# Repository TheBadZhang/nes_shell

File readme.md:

# 掌上 NES 游戏机
> 也不只是游戏机

基于 STM32H7B0VBT6 设计的 NES 掌上游戏机

包含 ESP8684 组成的 wifi 蓝牙 扩展
STM32G431CBU6 的可编程输入控制

本项目基于 weact stm32h7b0 开发板而来，主要用于学习 stm32h7b0 的使用。
移植了大量的有趣的程序，包括但不限于：

贪吃蛇、汉诺塔、俄罗斯方块

一些动画

ui效果

按键驱动

音频采集与输出

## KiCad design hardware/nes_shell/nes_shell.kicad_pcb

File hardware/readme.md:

archive       - 归档文件，一些废弃的工作
nes_shell     - 主板（包含主要计算功能）（不包含音频输入输出（可能考虑包含），不包含HDMI、VGA等显示输出）
key_board     - 按键子板（包含按键、LED、蜂鸣器等）
media_board   - 多媒体子板（包含音频输入输出、HDMI、VGA等显示输出）
pmod_extender - PMOD扩展板（包含PMOD接口）
screen_module_st7789 - st7789 屏幕模块（包含IPS LCD、WiFi、蓝牙、SD卡等）

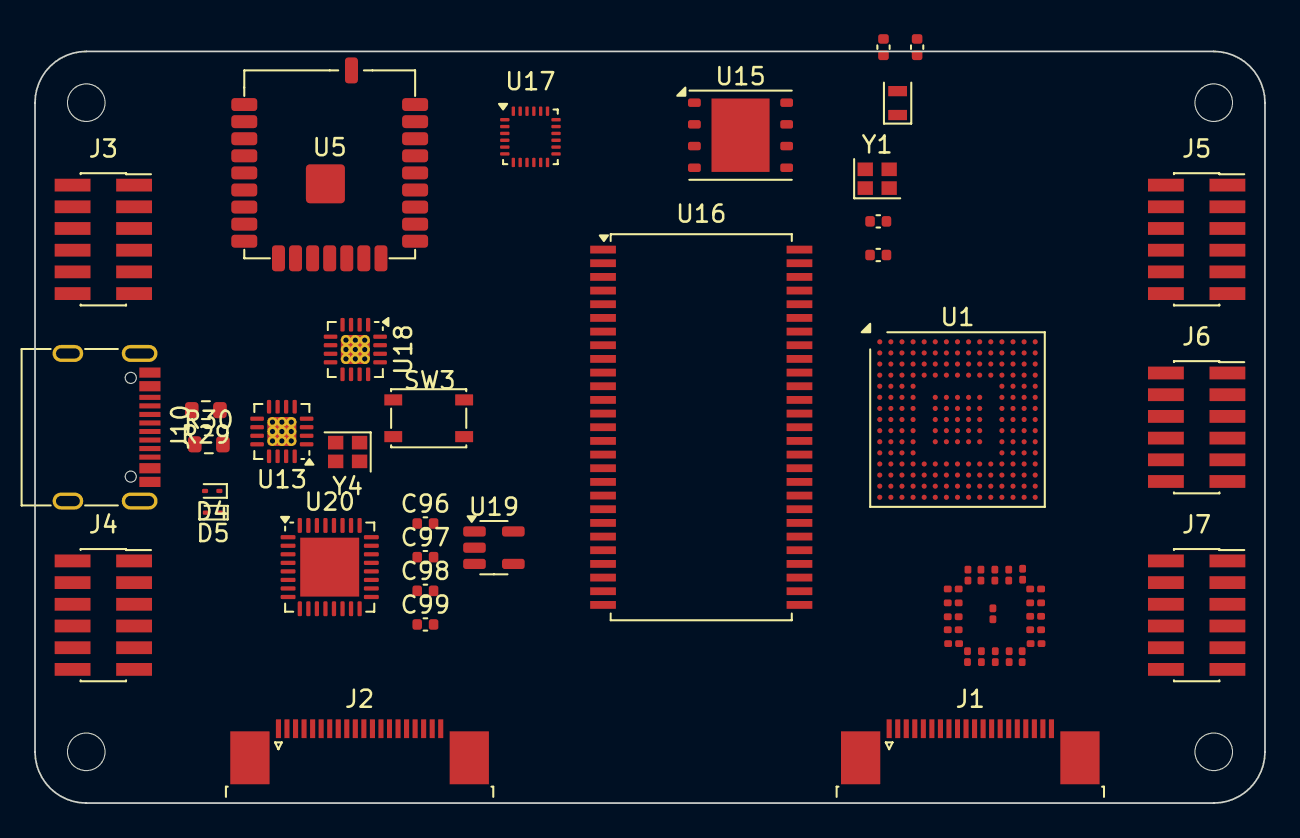
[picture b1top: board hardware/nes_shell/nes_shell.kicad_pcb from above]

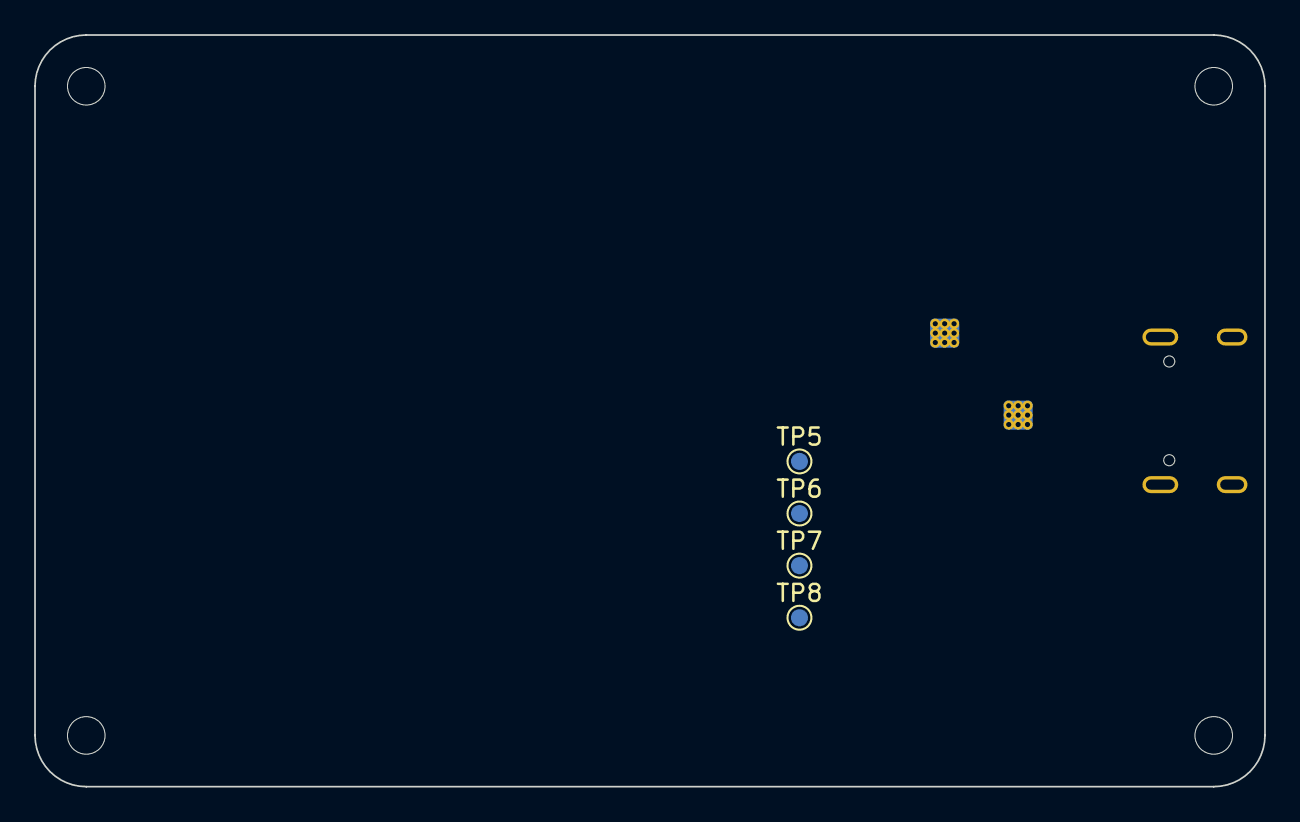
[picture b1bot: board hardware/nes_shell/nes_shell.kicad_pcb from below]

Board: 6 copper layers, 72.0 x 44.0 mm, 62 parts (4 on the bottom side), 23 nets, no tracks yet.

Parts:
C5, C18: 1.5pF; C_0402_1005Metric
C6, C7: 8pF; C_0402_1005Metric
C8, C9, C10, C11, C12, C13, C14, C15, C16, C17, C19, C20, C21, C22, C23, C24, C25, C26, C27, C28, C29: 0.1uF; C_0201_0603Metric
C96, C99: 4.7uF; C_0402_1005Metric
C97: 0.1uF; C_0402_1005Metric
C98: 22nF; C_0402_1005Metric
D4, D5: ESD9B3.3ST5G; D_SOD-923
H1, H2, H3, H4: MountingHole; MountingHole_2.2mm_M2
J1, J2: Conn_01x20_MountingPin; TE_2-1734839-0_1x20-1MP_P0.5mm_Horizontal
J3, J4, J5, J6, J7: Conn_02x06_Odd_Even; PinSocket_2x06_P1.27mm_Vertical_SMD
J10: USB_C_Receptacle_USB2.0_16P; USB_C_Receptacle_G-Switch_GT-USB-7010ASV
R29, R30: 5.1K; R_0603_1608Metric
SW3: SW_Push; KEY-SMD_4P-L4.2-W3.4-P2.15-LS4.5-TL
TP5: hub_ldo_3v3; TestPoint_Pad_D1.0mm
TP6: hub_gnd; TestPoint_Pad_D1.0mm
TP7: DMU; TestPoint_Pad_D1.0mm
TP8: DPU; TestPoint_Pad_D1.0mm
U1: STM32H7B0IBKxQ; UFBGA-201_10x10mm_Layout15x15_P0.65mm
U5: M0S
U13: CH334P; QFN-16-1EP_3x3mm_P0.5mm_EP1.7x1.7mm_ThermalVias
U15: W25Q32JVZP; WSON-8-1EP_6x5mm_P1.27mm_EP3.4x4.3mm
U16: MT48LC16M16A2TG; TSOP-II-54_22.2x10.16mm_P0.8mm
U17: MPU-9250; InvenSense_QFN-24_3x3mm_P0.4mm
U18: CH343P; QFN-16-1EP_3x3mm_P0.5mm_EP1.7x1.7mm_ThermalVias
U19: RT9193-33GB; SOT-23-5
U20: USB3300-EZK; QFN-32-1EP_5x5mm_P0.5mm_EP3.45x3.45mm
Y1: Crystal_GND24; Crystal_SMD_2016-4Pin_2.0x1.6mm
Y2: Crystal; Crystal_SMD_2012-2Pin_2.0x1.2mm
Y4: 12M; Crystal_SMD_2016-4Pin_2.0x1.6mm

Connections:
+1V8: U1.A3 (VDDLDO), U1.A13 (VDDLDO), U1.R14 (VDDLDO)
+3V3: C8.1, C9.1, C10.1, C11.1, C12.1, C13.1, C14.1, C15.1, C16.1, C17.1, C19.1, C20.1, C21.1, C22.1, C23.1, C24.1, C25.1, C26.1, C27.1, C28.1, C29.1, SW3.2, U1.D11 (VDD), U1.E4 (VDD), U1.E12 (VDD), U1.E15 (VDD50_USB), U1.F13 (VDD33_USB), U1.G4 (VDD), U1.H12 (VDD), U1.K4 (VDD), U1.L12 (VDD), U1.M5 (VDD), U1.M9 (VDD), U5.2 (VDD3V3), U15.8 (VCC), U16.1 (VDD), U16.3 (VDDQ), U16.9 (VDDQ), U16.14 (VDD), U16.27 (VDD), U16.43 (VDDQ), U16.49 (VDDQ)
/OSC32_IN: C5.1, U1.D2 (PC14), Y2.2
/OSC32_OUT: C18.1, U1.D1 (PC15), Y2.1
/OSC_IN: C6.1, U1.J1 (PH0), Y1.1
/OSC_OUT: C7.1, U1.K1 (PH1), Y1.3
/USB通信/CH343P/3V3: U18.3 (VDD5), U18.6 (V3), U18.9 (VBUS)
/USB通信/CH343P/D+: U13.8 (DP2), U18.7 (UD+)
/USB通信/CH343P/D-: U13.7 (DM2), U18.8 (UD-)
/USB通信/M0S-daplink/BOOT: SW3.1, U5.23 (GPIO2)
/USB通信/M0S-daplink/USB_DM: U5.13 (USB_DN), U13.9 (DM1)
/USB通信/M0S-daplink/USB_DP: U5.12 (USB_DP), U13.10 (DP1)
/USB通信/RT9193/+3V3: C99.2, TP5.1, U13.15 (V5), U13.16 (VDD33), U19.5 (Vout)
/USB通信/RT9193/+5V: C96.1, C97.1, U19.1 (Vin), U19.3 (EN)
/USB通信/USB_D+: D5.2 (A2), J10.A6 (D+), J10.B6 (D+), TP8.1, U13.12 (DPU)
/USB通信/USB_D-: D4.2 (A2), J10.A7 (D-), J10.B7 (D-), TP7.1, U13.11 (DMU)
GND: C5.2, C6.2, C7.2, C8.2, C9.2, C10.2, C11.2, C12.2, C13.2, C14.2, C15.2, C16.2, C17.2, C18.2, C19.2, C20.2, C21.2, C22.2, C23.2, C24.2, C25.2, C26.2, C27.2, C28.2, C29.2, C96.2, C97.2, C98.2, C99.1, D4.1 (A1), D5.1 (A1), J10.A1 (GND), J10.A12 (GND), J10.B1 (GND), J10.B12 (GND), J10.S1 (SHIELD), R29.1, R30.1, TP6.1, U1.A1 (VSS), U1.A15 (VSS), U1.C2 (VSS), U1.D6 (VSS), U1.D10 (VSS), U1.E1 (VSS), U1.F2 (VSSSMPS), U1.F6 (VSS), U1.F7 (VSS), U1.F8 (VSS), U1.F9 (VSS), U1.F10 (VSS), U1.F12 (VSS), U1.G6 (VSS), U1.G7 (VSS), U1.G8 (VSS), U1.G9 (VSS), U1.G10 (VSS), U1.H6 (VSS), U1.H7 (VSS), U1.H8 (VSS), U1.H9 (VSS), U1.H10 (VSS), U1.J6 (VSS), U1.J7 (VSS), U1.J8 (VSS), U1.J9 (VSS), U1.J10 (VSS), U1.J14 (VSS), U1.K2 (VSS), U1.K6 (VSS), U1.K7 (VSS), U1.K8 (VSS), U1.K9 (VSS), U1.K10 (VSS), U1.K12 (VSS), U1.M6 (VSS), U1.M10 (VSS), U1.N3 (VSSA), U1.R1 (VSS), U1.R15 (VSS), U5.1 (GND), U5.25 (GND), U5.27 (EPAD), U15.4 (GND), U15.9 (EP), U16.6 (VSSQ), U16.12 (VSSQ), U16.28 (VSS), U16.41 (VSS), U16.46 (VSSQ), U16.52 (VSSQ), U16.54 (VSS), U19.2 (GND), Y1.2, Y1.4, Y4.2, Y4.4
unnamed: J10.A5 (CC1), R29.2
unnamed: J10.B5 (CC2), R30.2
unnamed: U13.2 (XI), Y4.1
unnamed: U13.1 (XO), Y4.3
unnamed: C98.1, U19.4 (BP)
VBUS: J10.A4 (VBUS), J10.A9 (VBUS), J10.B4 (VBUS), J10.B9 (VBUS)

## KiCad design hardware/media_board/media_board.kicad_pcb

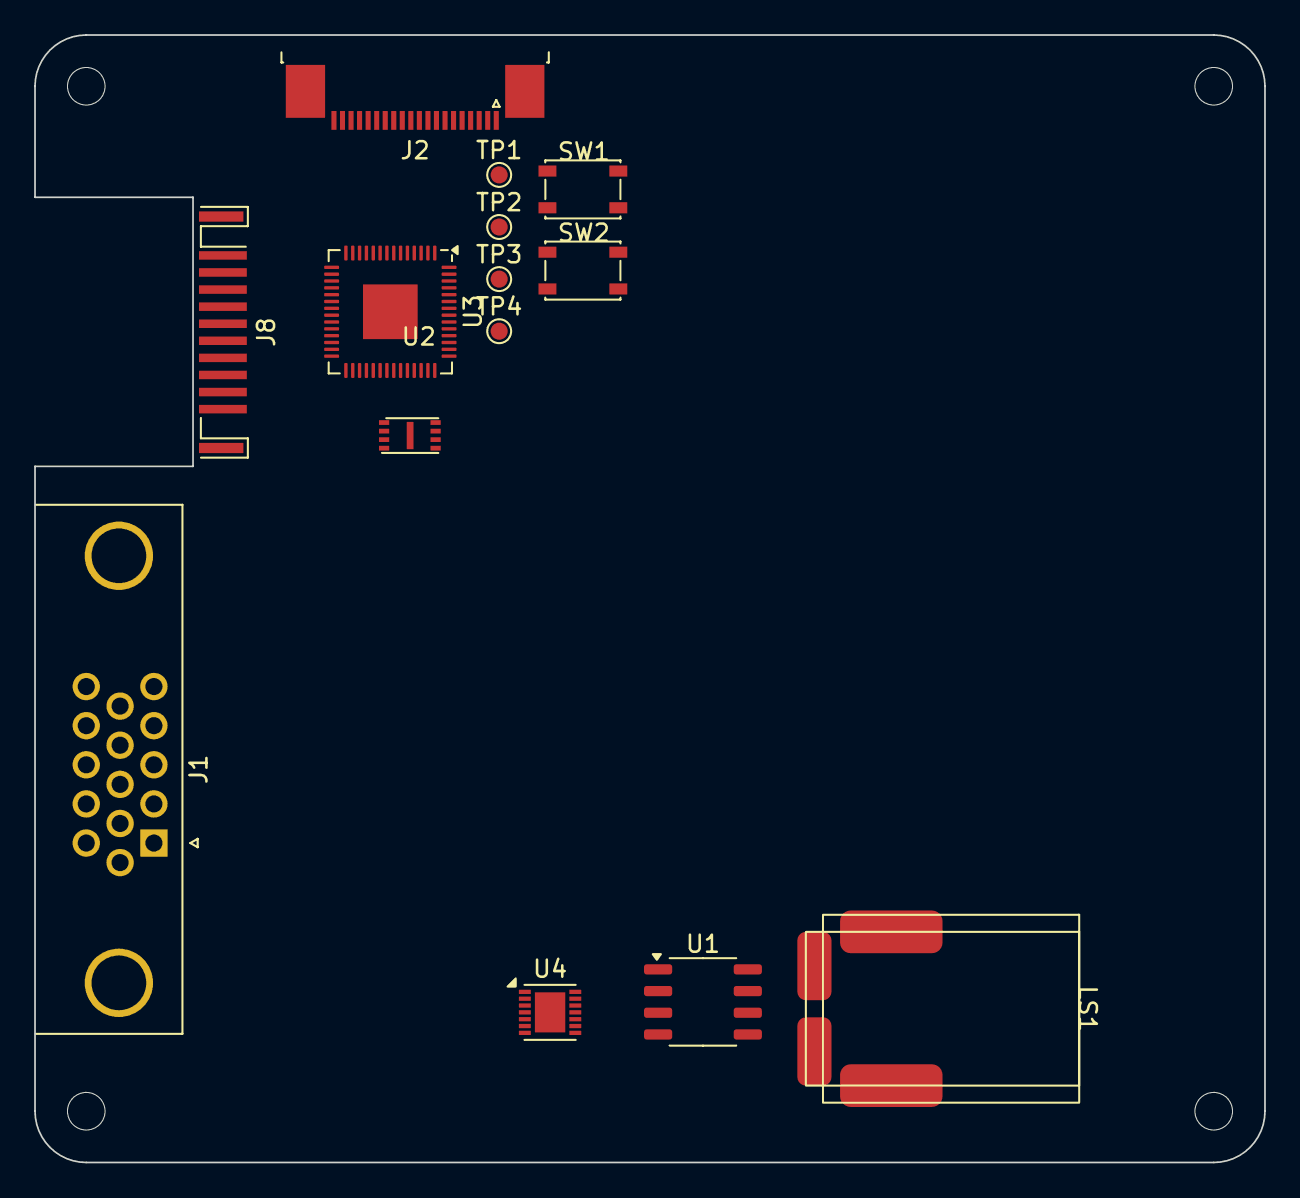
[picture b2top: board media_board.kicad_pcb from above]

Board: 2 copper layers, 72.0 x 66.0 mm, 18 parts (0 on the bottom side), 24 nets, no tracks yet.

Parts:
H1, H2, H3, H4: MountingHole; MountingHole_2.2mm_M2
J1: DE15_Plug_HighDensity_MountingHoles; DSUB-15-HD_Female_Horizontal_P2.29x1.98mm_EdgePinOffset3.03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
J2: Conn_01x20_MountingPin; TE_2-1734839-0_1x20-1MP_P0.5mm_Horizontal
J8: HDMI_A; HDMI_A_Contact_Technology_HDMI-19APL2_Horizontal
LS1: Speaker; speaker_1511_1609
SW1, SW2: SW_Push; KEY-SMD_4P-L4.2-W3.4-P2.15-LS4.5-TL
TP1, TP2, TP3, TP4: TestPoint; TestPoint_Pad_D1.0mm
U1: FM8002A; SOP-8_3.9x4.9mm_P1.27mm
U2: W25Q16; USON-8
U3: RP2040; QFN-56-1EP_7x7mm_P0.4mm_EP3.2x3.2mm
U4: MAX9814; DFN-14-1EP_3x3mm_P0.4mm_EP1.78x2.35mm

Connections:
+1V1: U3.23 (DVDD), U3.45 (VREG_VOUT), U3.50 (DVDD)
+3V3: TP1.1, U2.8 (VCC), U3.1 (IOVDD), U3.10 (IOVDD), U3.22 (IOVDD), U3.33 (IOVDD), U3.42 (IOVDD), U3.43 (ADC_AVDD), U3.44 (VREG_IN), U3.48 (USB_VDD), U3.49 (IOVDD), U4.2 (~SHDN), U4.5 (VDD)
/rp2040_hdmi/DVI_CK+: J8.10 (CK+), U3.12 (GPIO9)
/rp2040_hdmi/DVI_CK-: J8.12 (CK-), U3.11 (GPIO8)
/rp2040_hdmi/DVI_D0+: J8.7 (D0+), U3.14 (GPIO11)
/rp2040_hdmi/DVI_D0-: J8.9 (D0-), U3.13 (GPIO10)
/rp2040_hdmi/DVI_D1+: J8.4 (D1+), U3.16 (GPIO13)
/rp2040_hdmi/DVI_D1-: J8.6 (D1-), U3.15 (GPIO12)
/rp2040_hdmi/DVI_D2+: J8.1 (D2+), U3.18 (GPIO15)
/rp2040_hdmi/DVI_D2-: J8.3 (D2-), U3.17 (GPIO14)
/rp2040_hdmi/FLASH_SCK: U2.6 (CLK), U3.52 (QSPI_SCLK)
/rp2040_hdmi/FLASH_SD1: U2.2 (DO(IO1)), U3.55 (QSPI_SD1)
/rp2040_hdmi/FLASH_SD2: U2.3 (IO2), U3.54 (QSPI_SD2)
/rp2040_hdmi/FLASH_SD3: U2.7 (IO3), U3.51 (QSPI_SD3)
/rp2040_hdmi/FLASH_SDO: U2.5 (DI(IO0)), U3.53 (QSPI_SD0)
/rp2040_hdmi/FLASH_~CS: U2.1 (~CS), U3.56 (QSPI_SS)
/rp2040_hdmi/RUN_~RST: SW1.2, U3.26 (RUN)
/rp2040_hdmi/SWCLK: TP2.1, U3.24 (SWCLK)
/rp2040_hdmi/SWDIO: TP3.1, U3.25 (SWD)
/rp2040_hdmi/uC_DVI_SCL: J8.15 (SCL), U3.30 (GPIO19)
/rp2040_hdmi/uC_DVI_SDA: J8.16 (SDA), U3.29 (GPIO18)
GND: J1.0, J1.5, J1.6, J1.7, J1.8, J1.10, J8.2 (D2S), J8.5 (D1S), J8.8 (D0S), J8.11 (CKS), J8.17 (GND), J8.SH, SW1.1, SW2.1, TP4.1, U2.4 (GND), U3.19 (TESTEN), U3.57 (GND), U4.4 (GND), U4.7 (GND), U4.9 (A/R), U4.11 (GND), U4.15 (GND)
unnamed: LS1.1, U1.8 (VO2)
unnamed: LS1.2, U1.5 (VOI1)

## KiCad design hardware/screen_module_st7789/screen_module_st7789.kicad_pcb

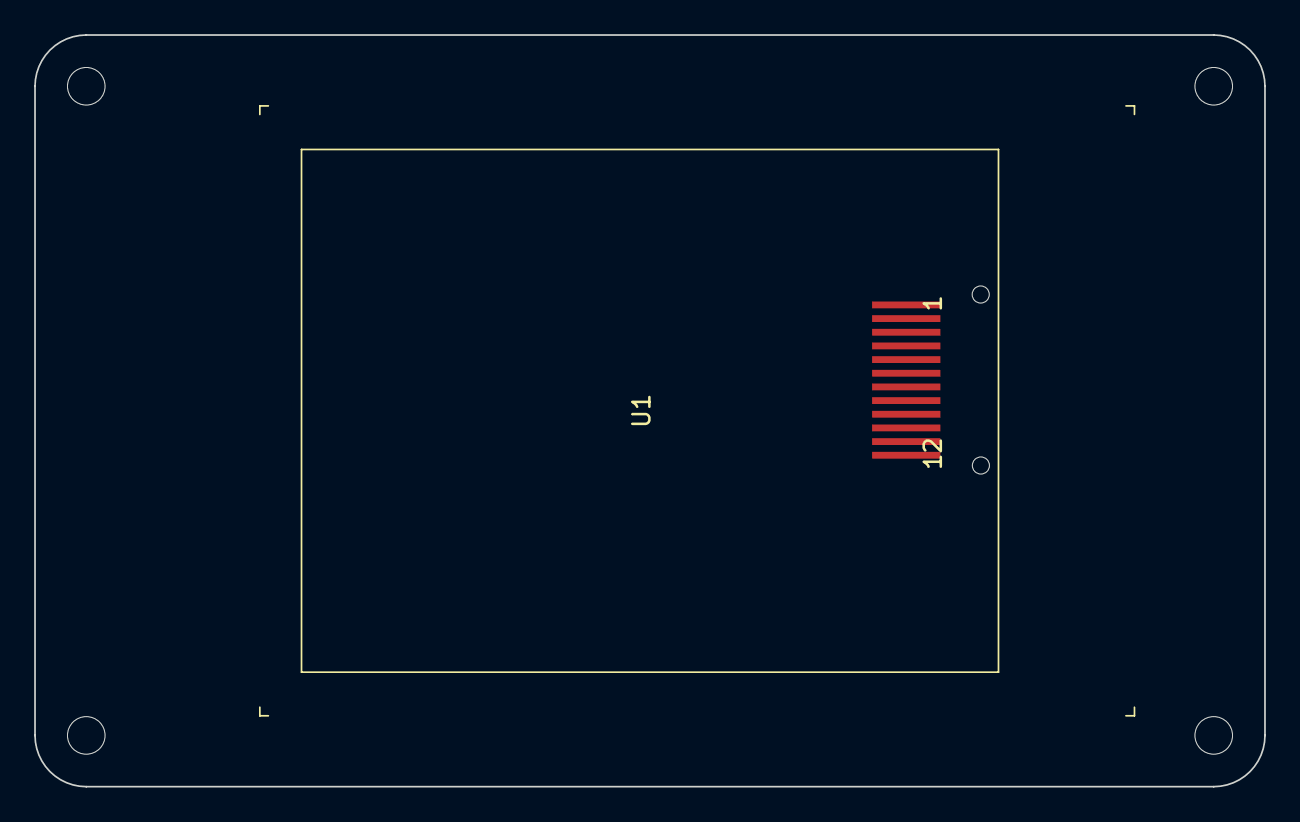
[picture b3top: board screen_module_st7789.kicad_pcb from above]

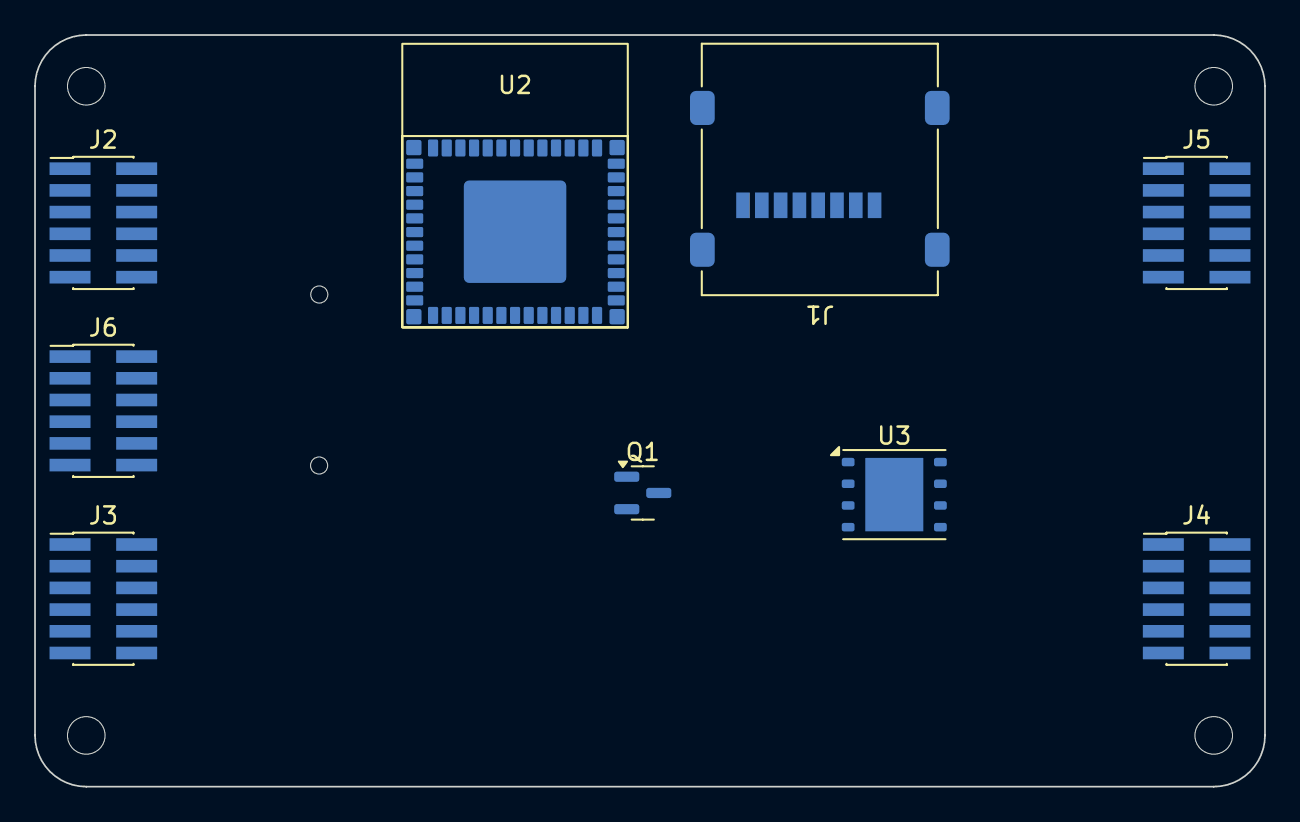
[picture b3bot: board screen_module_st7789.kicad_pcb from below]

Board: 2 copper layers, 72.0 x 44.0 mm, 14 parts (9 on the bottom side), 4 nets, no tracks yet.

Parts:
H1, H2, H3, H4: MountingHole; MountingHole_2.2mm_M2
J1: Micro_SD_Card; microSD_HC_Molex_47219-2001
J2, J3, J4, J5, J6: Conn_02x06_Odd_Even; PinHeader_2x06_P1.27mm_Vertical_SMD
Q1: S8050; SOT-23
U1: ips_2.0_240x320_12p
U2: esp32-c3-mini-1
U3: W25Q32JVZP; WSON-8-1EP_6x5mm_P1.27mm_EP3.4x4.3mm

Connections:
+3V3: J2.9, U3.8 (VCC)
/ESP32C3-MINI/GND: U2.1 (GND), U2.2 (GND), U2.11 (GND), U2.14 (GND), U2.36 (GND), U2.37 (GND), U2.38 (GND), U2.39 (GND), U2.40 (GND), U2.41 (GND), U2.42 (GND), U2.43 (GND), U2.44 (GND), U2.45 (GND), U2.46 (GND), U2.47 (GND), U2.48 (GND), U2.49 (GND), U2.50 (GND), U2.51 (GND), U2.52 (GND), U2.53 (GND)
GND: J2.11, J2.12, Q1.1 (E), U1.1 (GND1), U1.5 (GND2), U1.6 (GND3), U1.12 (GND4), U3.3 (IO2), U3.4 (GND), U3.7 (IO3), U3.9 (EP)
VCC: U1.3 (LEDA), U1.4 (VDD)

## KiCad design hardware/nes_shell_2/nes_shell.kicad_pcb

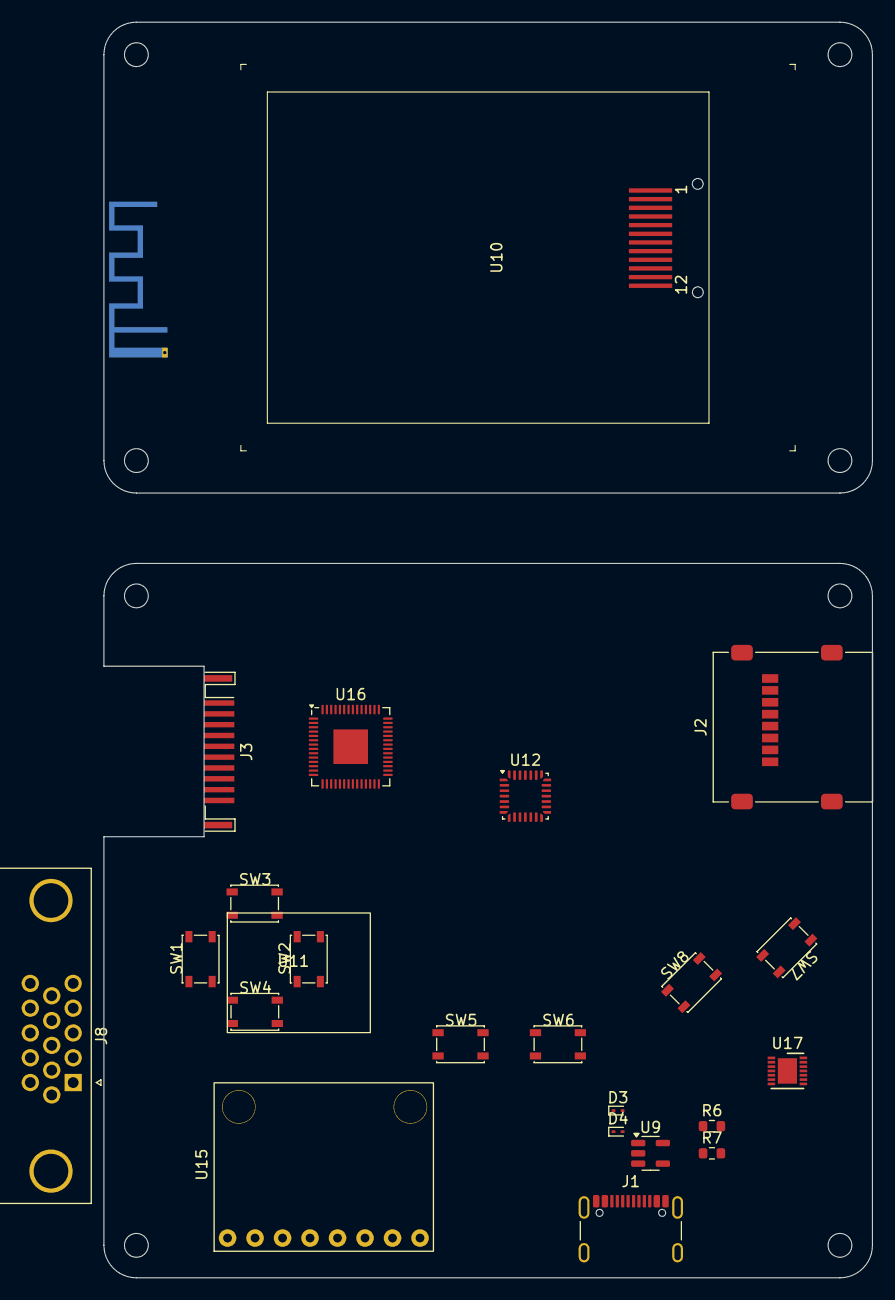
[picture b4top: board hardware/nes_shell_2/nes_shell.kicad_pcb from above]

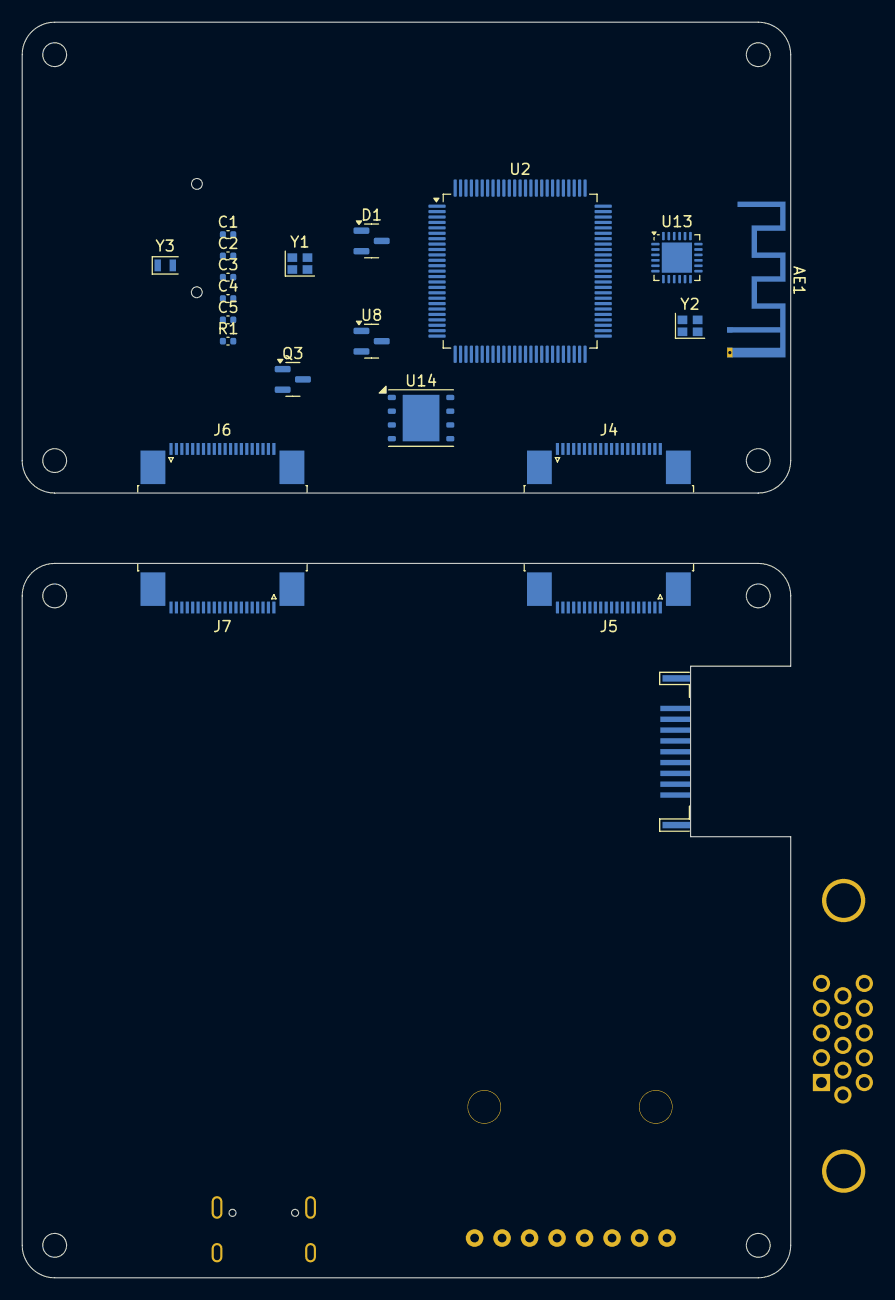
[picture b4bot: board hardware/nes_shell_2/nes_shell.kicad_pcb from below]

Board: 4 copper layers, 71.0 x 116.0 mm, 51 parts (20 on the bottom side), 30 nets, no tracks yet.

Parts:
AE1: Antenna_Chip; Texas_SWRA117D_2.4GHz_Left
C1, C2: 1.5pF; C_0402_1005Metric
C3, C4: 8pF; C_0402_1005Metric
C5: 100nF; C_0402_1005Metric
D1: BAT54C; SOT-23
D3, D4: ESD9B3.3ST5G; D_SOD-923
H1, H2, H3, H4, H5, H6, H7, H8: MountingHole; MountingHole_2.2mm_M2
J1: USB_C_Receptacle_USB2.0; USB_C_Receptacle_GCT_USB4105-xx-A_16P_TopMnt_Horizontal
J2: Micro_SD_Card; microSD_HC_Molex_47219-2001
J3: HDMI_A; HDMI_A_Contact_Technology_HDMI-19APL2_Horizontal
J4, J5, J6, J7: Conn_01x20_MountingPin; TE_2-1734839-0_1x20-1MP_P0.5mm_Horizontal
J8: DE15_Plug_HighDensity_MountingHoles; DSUB-15-HD_Female_Horizontal_P2.29x1.98mm_EdgePinOffset3.03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
Q3: S8050; SOT-23
R1: 10k; C_0402_1005Metric
R6, R7: 5.1K; R_0603_1608Metric
SW1, SW2, SW3, SW4, SW5, SW6, SW7, SW8: SW_Push; KEY-SMD_4P-L4.2-W3.4-P2.15-LS4.5-TL
U2: STM32H7B0VBTx; LQFP-100_14x14mm_P0.5mm
U8: REF3033; SOT-23
U9: RT9193-33GB; SOT-23-5
U10: ips_2.0_240x320_12p
U11: ns_joystick
U12: STM32G031G8Ux; QFN-28_4x4mm_P0.5mm
U13: QFN-24-1EP_4x4mm_P0.5mm_EP2.8x2.8mm
U14: W25Q32JVZP; WSON-8-1EP_6x5mm_P1.27mm_EP3.4x4.3mm
U15: MPU6050
U16: RP2040; QFN-56-1EP_7x7mm_P0.4mm_EP3.2x3.2mm
U17: MAX9814; DFN-14-1EP_3x3mm_P0.4mm_EP1.78x2.35mm
Y1, Y2: Crystal_GND24; Crystal_SMD_2016-4Pin_2.0x1.6mm
Y3: Crystal; Crystal_SMD_2012-2Pin_2.0x1.2mm

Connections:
/BOOT0: R1.1, U2.94 (BOOT0)
/IPS_CS: U2.3 (PE4), U10.8 (CS)
/IPS_DC: U2.2 (PE3), U10.7 (D/C)
/IPS_RST: U2.98 (PE1), U10.11 (RES)
/IPS_SCL: U2.1 (PE2), U10.9 (SCL)
/IPS_SDA: U2.5 (PE6), U10.10 (SDA)
/NRST: C5.1, U2.14 (NRST)
/OSC32_IN: C1.1, U2.8 (PC14), Y3.2
/OSC32_OUT: C2.1, U2.9 (PC15), Y3.1
/OSC_IN: C3.1, U2.12 (PH0), Y1.1
/OSC_OUT: C4.1, U2.13 (PH1), Y1.3
/SD1_CLK: J2.5 (CLK), U2.80 (PC12)
/SD1_CMD: J2.3 (CMD), U2.83 (PD2)
/SD1_D0: J2.7 (DAT0), U2.65 (PC8)
/SD1_D1: J2.8 (DAT1), U2.66 (PC9)
/SD1_D2: J2.1 (DAT2), U2.78 (PC10)
/SD1_D3: J2.2 (DAT3/CD), U2.79 (PC11)
/VBAT: D1.3, U2.6 (VBAT)
/VREF+: U2.20 (VREF+), U8.2 (OUT)
/usb1_D+: D3.2 (A2), J1.A6 (D+), J1.B6 (D+)
/usb1_D-: D4.2 (A2), J1.A7 (D-), J1.B7 (D-)
GND: C1.2, C2.2, C3.2, C4.2, C5.2, D3.1 (A1), D4.1 (A1), J1.A1 (GND), J1.A12 (GND), J1.B1 (GND), J1.B12 (GND), J1.S1 (SHIELD), Q3.1 (E), R1.2, R6.1, R7.1, U2.10 (VSS), U2.19 (VSSA), U2.26 (VSS), U2.49 (VSS), U2.74 (VSS), U2.99 (VSS), U8.3 (GND), U10.1 (GND1), U10.5 (GND2), U10.6 (GND3), U10.12 (GND4), Y1.2, Y1.4
unnamed: J1.A5 (CC1), R6.2
unnamed: J1.B5 (CC2), R7.2
unnamed: U16.23 (DVDD), U16.50 (DVDD)
unnamed: U16.1 (IOVDD), U16.10 (IOVDD), U16.22 (IOVDD), U16.33 (IOVDD), U16.42 (IOVDD), U16.49 (IOVDD)
unnamed: U17.4 (GND), U17.7 (GND), U17.11 (GND), U17.15 (GND)
VBUS: J1.A4 (VBUS), J1.A9 (VBUS), J1.B4 (VBUS), J1.B9 (VBUS)
VCC: U10.3 (LEDA), U10.4 (VDD)
VDD: D1.1, U2.11 (VDD), U2.27 (VDD), U2.50 (VDD), U2.75 (VDD), U2.100 (VDD), U8.1 (IN)

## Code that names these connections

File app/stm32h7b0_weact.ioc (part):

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Mcu.Name=STM32H7B0VBTx
Mcu.Package=LQFP100
Mcu.UserName=STM32H7B0VBTx
PA0.Mode=Asynchronous
PA0.Signal=UART4_TX
PA1.Mode=Asynchronous
PA1.Signal=UART4_RX
PA10.Mode=Asynchronous
PA10.Signal=USART1_RX
PA11.Mode=Device_Only_FS
PA11.Signal=USB_OTG_HS_DM
PA12.Mode=Device_Only_FS
PA12.Signal=USB_OTG_HS_DP
PA13.Mode=Serial_Wire
PA13.Signal=DEBUG_JTMS-SWDIO
PA14.Mode=Serial_Wire
PA14.Signal=DEBUG_JTCK-SWCLK
PA15.GPIOParameters=GPIO_PuPd,GPIO_Label
PA15.GPIO_Label=C1
PA15.GPIO_PuPd=GPIO_PULLDOWN
PA15.Signal=GPIO_Input
PA4.Mode=Slave_8_bits_External_Synchro
PA4.Signal=DCMI_HSYNC
PA5.GPIOParameters=GPIO_Label
PA5.GPIO_Label=M_SCK
PA5.Mode=TX_Only_Simplex_Unidirect_Master
PA5.Signal=SPI6_SCK
PA6.Mode=Slave_8_bits_External_Synchro
PA6.Signal=DCMI_PIXCLK
PA7.GPIOParameters=GPIO_Label
PA7.GPIO_Label=M_SDA
PA7.Mode=TX_Only_Simplex_Unidirect_Master
PA7.Signal=SPI6_MOSI
PA8.Mode=Clock-out-1
PA8.Signal=RCC_MCO_1
PA9.Mode=Asynchronous
PA9.Signal=USART1_TX
PB1.GPIOParameters=GPIO_Label
PB1.GPIO_Label=AR
PB1.Signal=GPIO_Output
PB10.Mode=I2C
PB10.Signal=I2C2_SCL
PB11.Mode=I2C
PB11.Signal=I2C2_SDA
PB12.GPIOParameters=GPIO_PuPd,GPIO_Label
PB12.GPIO_Label=C5
PB12.GPIO_PuPd=GPIO_PULLDOWN
PB12.Signal=GPIO_Input
PB13.GPIOParameters=GPIO_PuPd,GPIO_Label
PB13.GPIO_Label=C4
PB13.GPIO_PuPd=GPIO_PULLDOWN
PB13.Signal=GPIO_Input
PB14.GPIOParameters=GPIO_PuPd,GPIO_Label
PB14.GPIO_Label=C3
PB14.GPIO_PuPd=GPIO_PULLDOWN
PB14.Signal=GPIO_Input
PB15.GPIOParameters=GPIO_PuPd,GPIO_Label
PB15.GPIO_Label=C2
PB15.GPIO_PuPd=GPIO_PULLDOWN
PB15.Signal=GPIO_Input
PB2.Signal=OCTOSPIM_P1_CLK
PB3.Mode=Full_Duplex_Master
PB3.Signal=SPI1_SCK
PB4.Mode=Full_Duplex_Master
PB4.Signal=SPI1_MISO
PB5.GPIOParameters=GPIO_Speed,GPIO_Label
PB5.GPIO_Label=M_DC
PB5.GPIO_Speed=GPIO_SPEED_FREQ_VERY_HIGH
PB5.Signal=GPIO_Output
PB6.Signal=OCTOSPIM_P1_NCS
PB7.Mode=Slave_8_bits_External_Synchro
PB7.Signal=DCMI_VSYNC
PB8.Mode=I2C
PB8.Signal=I2C1_SCL
PB9.Mode=I2C
PB9.Signal=I2C1_SDA
PC10.Mode=SD_4_bits_Wide_bus
PC10.Signal=SDMMC1_D2
PC11.Mode=SD_4_bits_Wide_bus
PC11.Signal=SDMMC1_D3
PC12.Mode=SD_4_bits_Wide_bus
PC12.Signal=SDMMC1_CK
PC13.GPIOParameters=GPIO_Label
PC13.GPIO_Label=K1
PC13.Signal=GPIO_Output
PC14-OSC32_IN.Mode=LSE-External-Oscillator
PC14-OSC32_IN.Signal=RCC_OSC32_IN
PC15-OSC32_OUT.Mode=LSE-External-Oscillator
PC15-OSC32_OUT.Signal=RCC_OSC32_OUT
PC4.GPIOParameters=GPIO_Label
PC4.GPIO_Label=GAIN
PC4.Signal=GPIO_Output
PC5.Signal=ADCx_INP8
PC6.Mode=Slave_8_bits_External_Synchro
PC6.Signal=DCMI_D0
PC7.Mode=Slave_8_bits_External_Synchro
PC7.Signal=DCMI_D1
PC8.Mode=SD_4_bits_Wide_bus
PC8.Signal=SDMMC1_D0
PC9.Mode=SD_4_bits_Wide_bus
PC9.Signal=SDMMC1_D1
PD0.GPIOParameters=GPIO_Speed,GPIO_Label
PD0.GPIO_Label=M_RST
PD0.GPIO_Speed=GPIO_SPEED_FREQ_VERY_HIGH
PD0.Signal=GPIO_Output
PD10.GPIOParameters=GPIO_PuPd,GPIO_Label
PD10.GPIO_Label=R1
PD10.GPIO_PuPd=GPIO_NOPULL
PD10.Signal=GPIO_Output
PD11.Signal=OCTOSPIM_P1_IO0
PD12.Signal=OCTOSPIM_P1_IO1
PD13.Signal=OCTOSPIM_P1_IO3
PD2.Mode=SD_4_bits_Wide_bus
PD2.Signal=SDMMC1_CMD
PD3.Mode=Slave_8_bits_External_Synchro
PD3.Signal=DCMI_D5
PD5.GPIOParameters=GPIO_Speed,GPIO_Label
PD5.GPIO_Label=M_CS
PD5.GPIO_Speed=GPIO_SPEED_FREQ_VERY_HIGH
PD5.Signal=GPIO_Output
PD6.GPIOParameters=GPIO_Label
PD6.GPIO_Label=SPI1_CS
PD6.Signal=GPIO_Output
PD7.Mode=Full_Duplex_Master
PD7.Signal=SPI1_MOSI
PD8.GPIOParameters=GPIO_Label
PD8.GPIO_Label=R3
PD8.Signal=GPIO_Output
PD9.GPIOParameters=GPIO_PuPd,GPIO_Label
PD9.GPIO_Label=R2
PD9.GPIO_PuPd=GPIO_NOPULL
PD9.Signal=GPIO_Output
PE0.Mode=Slave_8_bits_External_Synchro
PE0.Signal=DCMI_D2
PE1.Mode=Slave_8_bits_External_Synchro
PE1.Signal=DCMI_D3
PE10.GPIOParameters=GPIO_Label
PE10.GPIO_Label=LCD_LED
PE10.Signal=GPIO_Output
PE11.GPIOParameters=GPIO_Label
PE11.GPIO_Label=CS1
PE11.Signal=GPIO_Output
PE12.GPIOParameters=GPIO_Label
PE12.GPIO_Label=SCK1
PE12.Mode=TX_Only_Simplex_Unidirect_Master
PE12.Signal=SPI4_SCK
PE13.GPIOParameters=GPIO_Label
PE13.GPIO_Label=DC1
PE13.Signal=GPIO_Output
PE14.GPIOParameters=GPIO_Label
PE14.GPIO_Label=SDA1
PE14.Mode=TX_Only_Simplex_Unidirect_Master
PE14.Signal=SPI4_MOSI
PE15.GPIOParameters=GPIO_Label
PE15.GPIO_Label=RST1
PE15.Signal=GPIO_Output
PE2.Signal=OCTOSPIM_P1_IO2
PE3.GPIOParameters=GPIO_Label
PE3.GPIO_Label=LED
PE3.Signal=GPIO_Output
PE4.Mode=Slave_8_bits_External_Synchro
PE4.Signal=DCMI_D4
PE5.Mode=Slave_8_bits_External_Synchro
PE5.Signal=DCMI_D6
PE6.Mode=Slave_8_bits_External_Synchro
PE6.Signal=DCMI_D7
PH0-OSC_IN.Mode=HSE-External-Oscillator
PH0-OSC_IN.Signal=RCC_OSC_IN
PH1-OSC_OUT.Mode=HSE-External-Oscillator
PH1-OSC_OUT.Signal=RCC_OSC_OUT
RCC.HSE_VALUE=25000000
RCC.SYSCLKFreq_VALUE=280000000
RCC.SYSCLKSource=RCC_SYSCLKSOURCE_PLLCLK
board=custom

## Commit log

2024-01-21 初始化git库，记录修改
2024-01-21 部分代码移入 codebase
2024-01-21 将部分操作整理成类以便移植
2024-01-21 优化了框架结构，增加了更多的动画效果
2024-01-22 把通用部分移入codebase 尝试解决bmda2的问题，u8g2难以解决，遂放弃
2024-01-24 实现了动态APP图标的功能
2024-01-24 给APP添加了动态图标的功能
2024-01-24 给时钟APP添加了更为合适的动态app图标
2024-01-24 删除了不需要的APP间跳转
    现在可以直接通过 main_app 进行有选择的跳转，而不需要这样使用状态机了
2024-01-25 添加了 RTC 时钟，使LIST独立为一个类
2024-01-25 使 APP 选择器成为单实例
2024-01-25 ADC DMA在ADC中打开DMA请求才可以使用DMA循环采集
2024-01-25 解决了DMA ADC读取的问题
2024-01-26 成功移植 SOUND_WAVE 工程
2024-01-26 给代码添加了 tinyexpr 和 lua 的支持
2024-01-26 更新了lua的支持
2024-01-27 优化了数据拷贝造成的FFT频谱泄露的问题
2024-01-27 更换了OLED的刷新函数
    将u8g2的buffer转换成oled原始数据，然后整体打包发送。打包发送提升了性能，但是转换的过程仍然用了不少时间。DMA还是无法使用，性能提升有限。帧率提升大概是20%左右。可能存在更优的转换函数或者自己实现所有的绘制，不使用u8g2
2024-01-27 优化了代码结构
2024-01-27 sound_wave 完全不依赖U8G2了
2024-01-28 尝试加了一些format库，但都不能直接工作，遂放弃
2024-01-29 灰度图片显示测试
2024-01-29 实现了不同源绘制分离
2024-01-29 添加了动态蜘蛛网的背景动效
2024-01-30 修正了OLED显示的异常 增加了3D骰子渲染的DEMO
2024-01-30 将todo移了出去
2024-02-01 项目初始化提交
2024-02-01 修复了OLED电感啸叫的问题
2024-02-01 添加了一些待做
2024-02-01 硬件设计的两个版本
    竖版横版
2024-02-01 修改了游戏机的布局、添加了一些元件
2024-02-02 删除了没用的文件
2024-02-02 整理了一些代码，进一步与 u8g2 解耦
2024-02-03 添加了流传输的支持，可惜slogic的daplink状态下的串口速度太慢了
2024-02-03 删除了多余的文件、优化了目录结构
2024-02-03 使用网上的图片素材代替了按键效果
2024-02-03 添加了一些不用提交的文件
2024-02-04 添加了对LCD240320的支持
2024-02-04 将st7789和ssd1327的驱动抽象了出来
2024-02-04 st7789 移植 over
2024-02-05 移除了一些暂时用不到的库
2024-02-05 成功修复了 st7789 独立工作的问题
2024-02-06 成功移植了 cherry usb 到项目中
2024-02-07 解耦代码
2024-02-29 添加了nespp模拟器内核为gitmodule
2024-02-29 add more ignored file
2024-02-29 other file commit
2024-04-06 在STM32H743上运行了infones，考虑将内存占用较高的部分移到ram中。处理好按键和音频输出
2024-04-14 归档旧的设计
2024-04-14 全新的分离设计，将不同的板子分在不同的项目当中
